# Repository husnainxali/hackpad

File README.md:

# Brokiepad – A 3x3 Macropad

### A simple and minimal 3*3 macropad with a built in oled display that can be customized to any use rn i have mapped it out as a gaming macropad using some of the basic keys that r needed while playing any game .

---
## Renders
- **PCB**

- **Case**

- **Explode view**

- **PCB layout**

- **Schematic**
 
<p align="center">
  <br>
 </p>

  ---
## BOM

Full parts list with quantities and costs: **[BOM.csv](BOM.csv)**

---
### Features:

- **9 Mechanical Switches**
- **OLED Display** 
- **12 SK6812MINI-E LEDs**
- **QMK Firmware**
- **Custom KiCad PCB**
- **3D-Printed Case**

---

## Keymap rn 

| Row | Key 1 | Key 2 | Key 3 |
|-----|-------|-------|-------|
| **1** | G | W | R |
| **2** | A | S | D |
| **3** | Left Shift | Space | Left Ctrl |

---
## Getting Started
- **Download PCB files and edit them according to your own need**
- **Download QMK MSYS**
- **Install Python and run `python3 -m pip install qmk` and then run `qmk setup` in terminal**
- **Download **[Brokiepad.uf2](Production/brokiepad.uf2)****
- **connect your macropad with a pc using a cable** 
- **Hold the boot button on the RP2040 board.**
- **Keep holding it while you plug the USB cable into your PC, then release the button.**
- **A drive named RPI-RP2 appears in File Explorer.**
- **Drag and drop your .uf2 file onto that drive.**
- **The drive disappears by itself after a few seconds and the board reboots as your macropad.**
- 
This project is licensed under the [MIT License](LICENSE).

---

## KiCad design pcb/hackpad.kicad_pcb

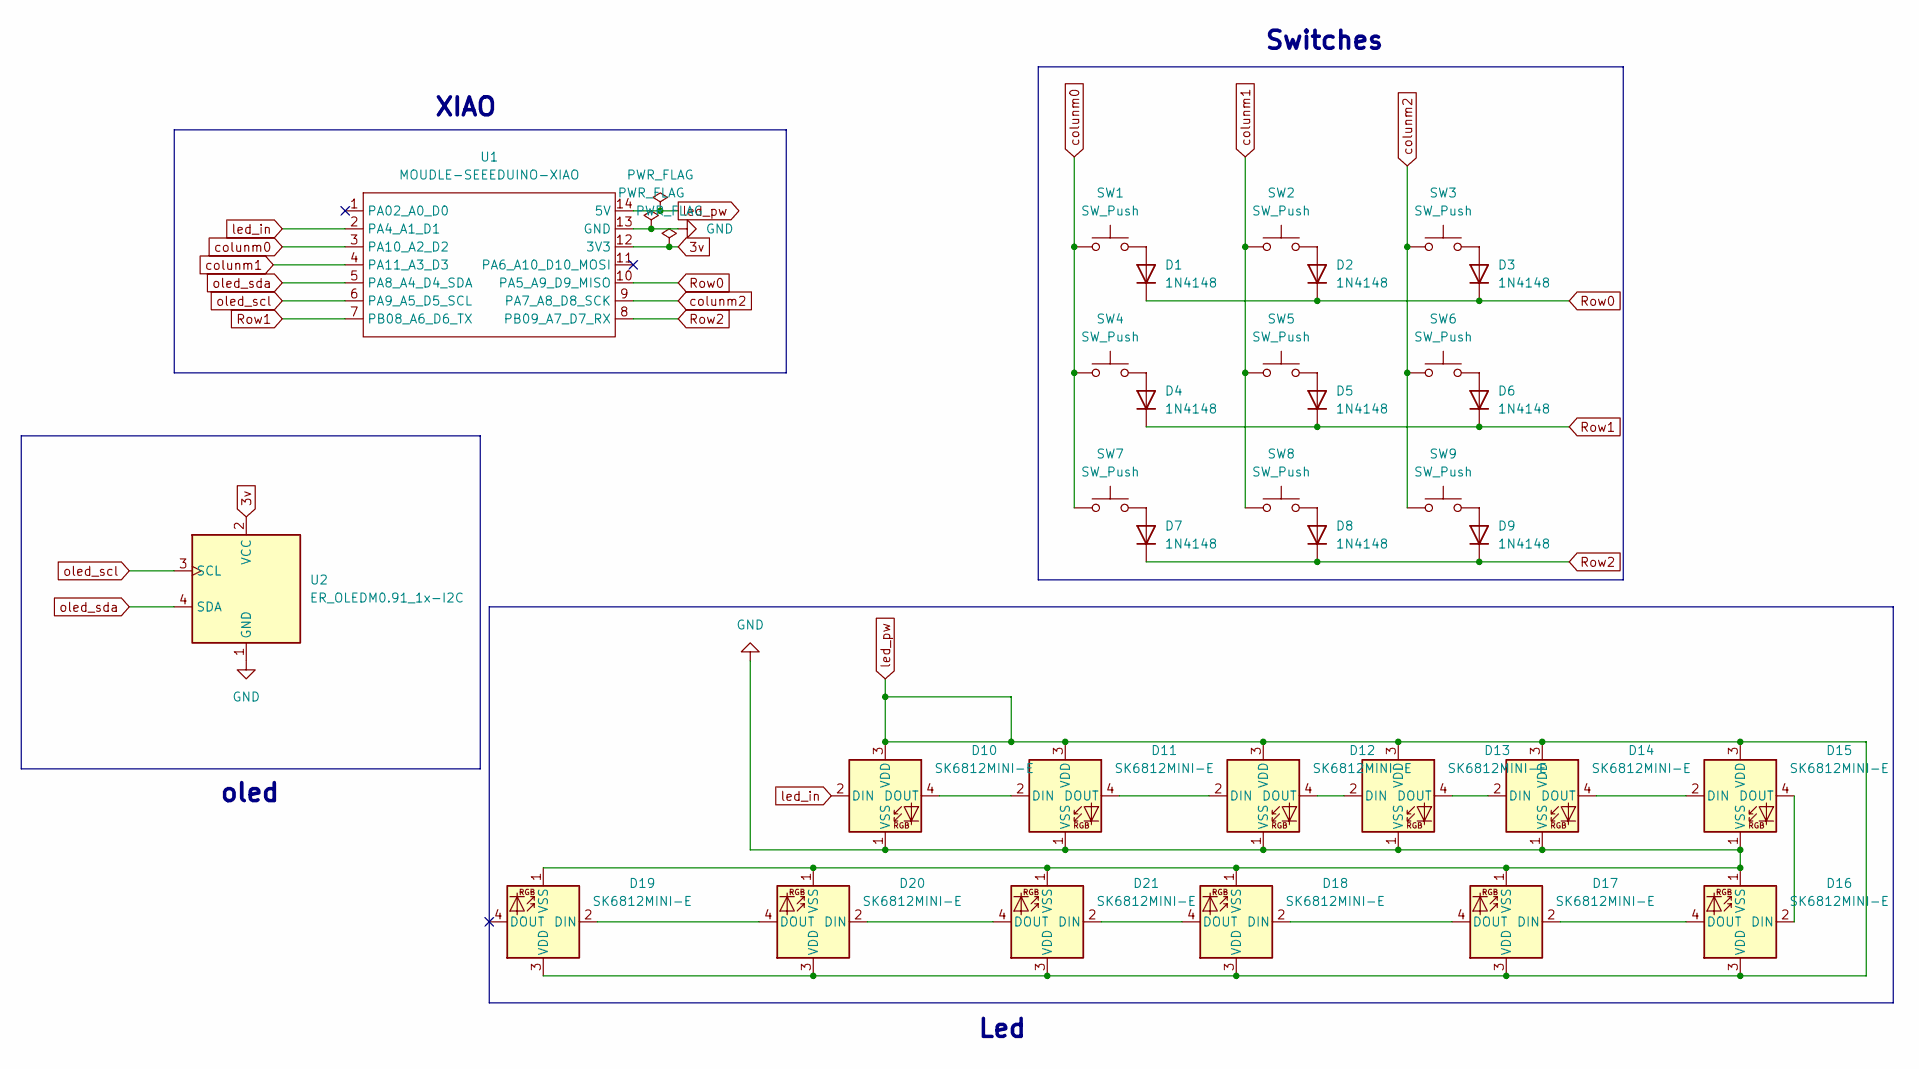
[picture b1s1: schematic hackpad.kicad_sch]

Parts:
D1, D2, D3, D4, D5, D6, D7, D8, D9: 1N4148; D_DO-35_SOD27_P7.62mm_Horizontal
D10, D11, D12, D13, D14, D15, D16, D17, D18, D19, D20, D21: SK6812MINI-E; LED_SK6812MINI-E_3.2x2.8mm_P1.5mm_ReverseMount
SW1, SW2, SW3, SW4, SW5, SW6, SW7, SW8, SW9: SW_Push; SW_Cherry_MX_1.00u_PCB
U1: MOUDLE-SEEEDUINO-XIAO; XIAO-Generic-Hybrid-14P-2.54-21X17.8MM
U2: ER_OLEDM0.91_1x-I2C

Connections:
3v: U1.12 (3V3), U2.2 (VCC)
GND: D10.1 (VSS), D11.1 (VSS), D12.1 (VSS), D13.1 (VSS), D14.1 (VSS), D15.1 (VSS), D16.1 (VSS), D17.1 (VSS), D18.1 (VSS), D19.1 (VSS), D20.1 (VSS), D21.1 (VSS), U1.13 (GND), U2.1 (GND)
unnamed: D1.2 (A), SW1.2
unnamed: D2.2 (A), SW2.2
unnamed: D3.2 (A), SW3.2
unnamed: D4.2 (A), SW4.2
unnamed: D5.2 (A), SW5.2
unnamed: D6.2 (A), SW6.2
unnamed: D7.2 (A), SW7.2
unnamed: D8.2 (A), SW8.2
unnamed: D9.2 (A), SW9.2
unnamed: D10.4 (DOUT), D11.2 (DIN)
unnamed: D11.4 (DOUT), D12.2 (DIN)
unnamed: D12.4 (DOUT), D13.2 (DIN)
unnamed: D13.4 (DOUT), D14.2 (DIN)
unnamed: D14.4 (DOUT), D15.2 (DIN)
unnamed: D15.4 (DOUT), D16.2 (DIN)
unnamed: D16.4 (DOUT), D17.2 (DIN)
unnamed: D17.4 (DOUT), D18.2 (DIN)
unnamed: D18.4 (DOUT), D21.2 (DIN)
unnamed: D19.2 (DIN), D20.4 (DOUT)
unnamed: D20.2 (DIN), D21.4 (DOUT)
Row0: D1.1 (K), D2.1 (K), D3.1 (K), U1.10 (PA5_A9_D9_MISO)
Row1: D4.1 (K), D5.1 (K), D6.1 (K), U1.7 (PB08_A6_D6_TX)
Row2: D7.1 (K), D8.1 (K), D9.1 (K), U1.8 (PB09_A7_D7_RX)
colunm0: SW1.1, SW4.1, SW7.1, U1.3 (PA10_A2_D2)
colunm1: SW2.1, SW5.1, SW8.1, U1.4 (PA11_A3_D3)
colunm2: SW3.1, SW6.1, SW9.1, U1.9 (PA7_A8_D8_SCK)
led_in: D10.2 (DIN), U1.2 (PA4_A1_D1)
led_pw: D10.3 (VDD), D11.3 (VDD), D12.3 (VDD), D13.3 (VDD), D14.3 (VDD), D15.3 (VDD), D16.3 (VDD), D17.3 (VDD), D18.3 (VDD), D19.3 (VDD), D20.3 (VDD), D21.3 (VDD), U1.14 (5V)
oled_scl: U1.6 (PA9_A5_D5_SCL), U2.3 (SCL)
oled_sda: U1.5 (PA8_A4_D4_SDA), U2.4 (SDA)

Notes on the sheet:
Led
Switches
XIAO
oled

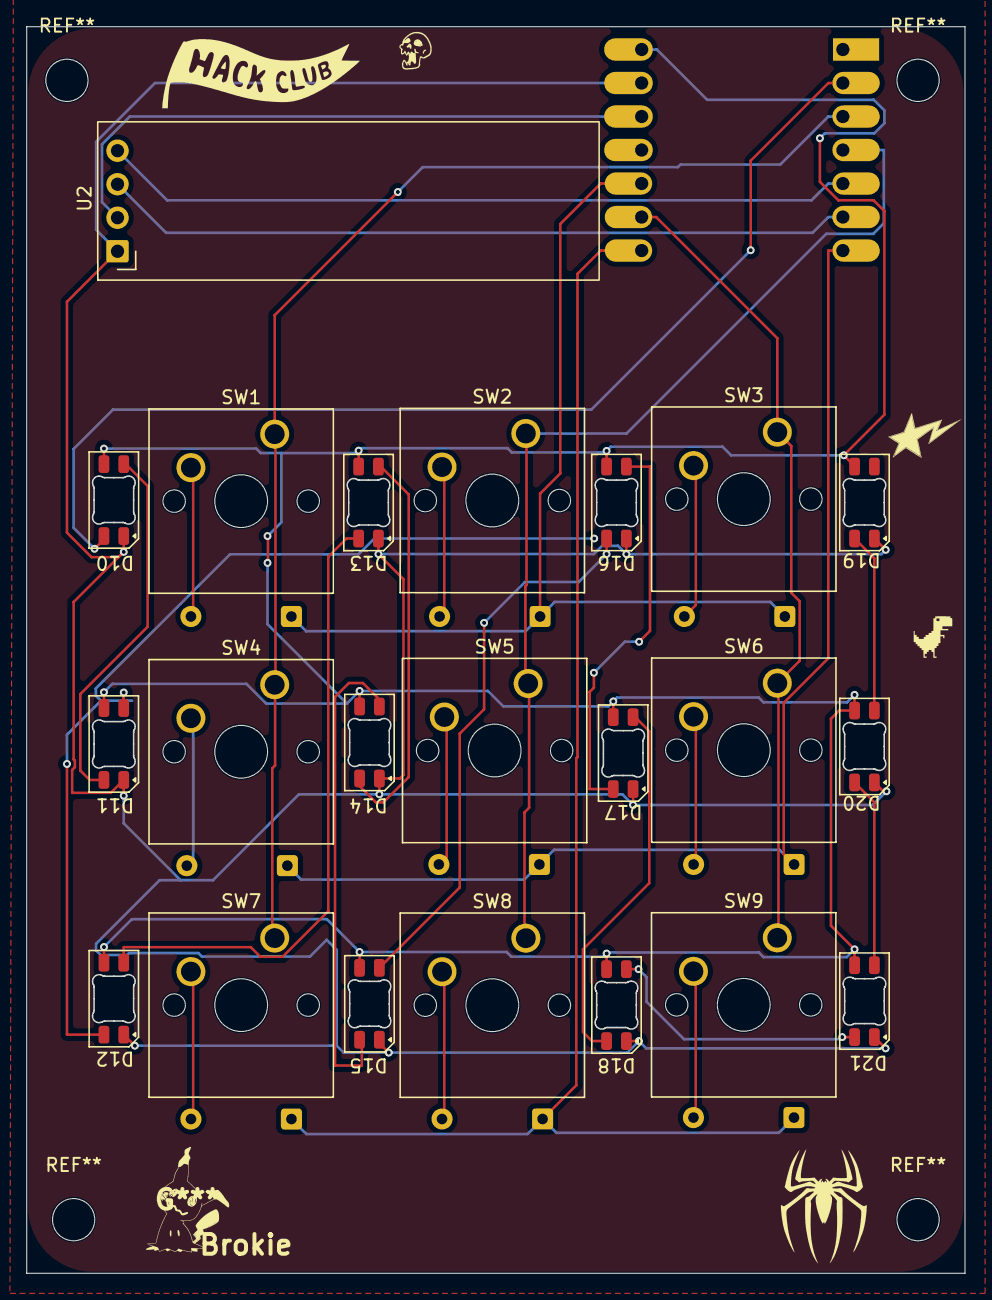
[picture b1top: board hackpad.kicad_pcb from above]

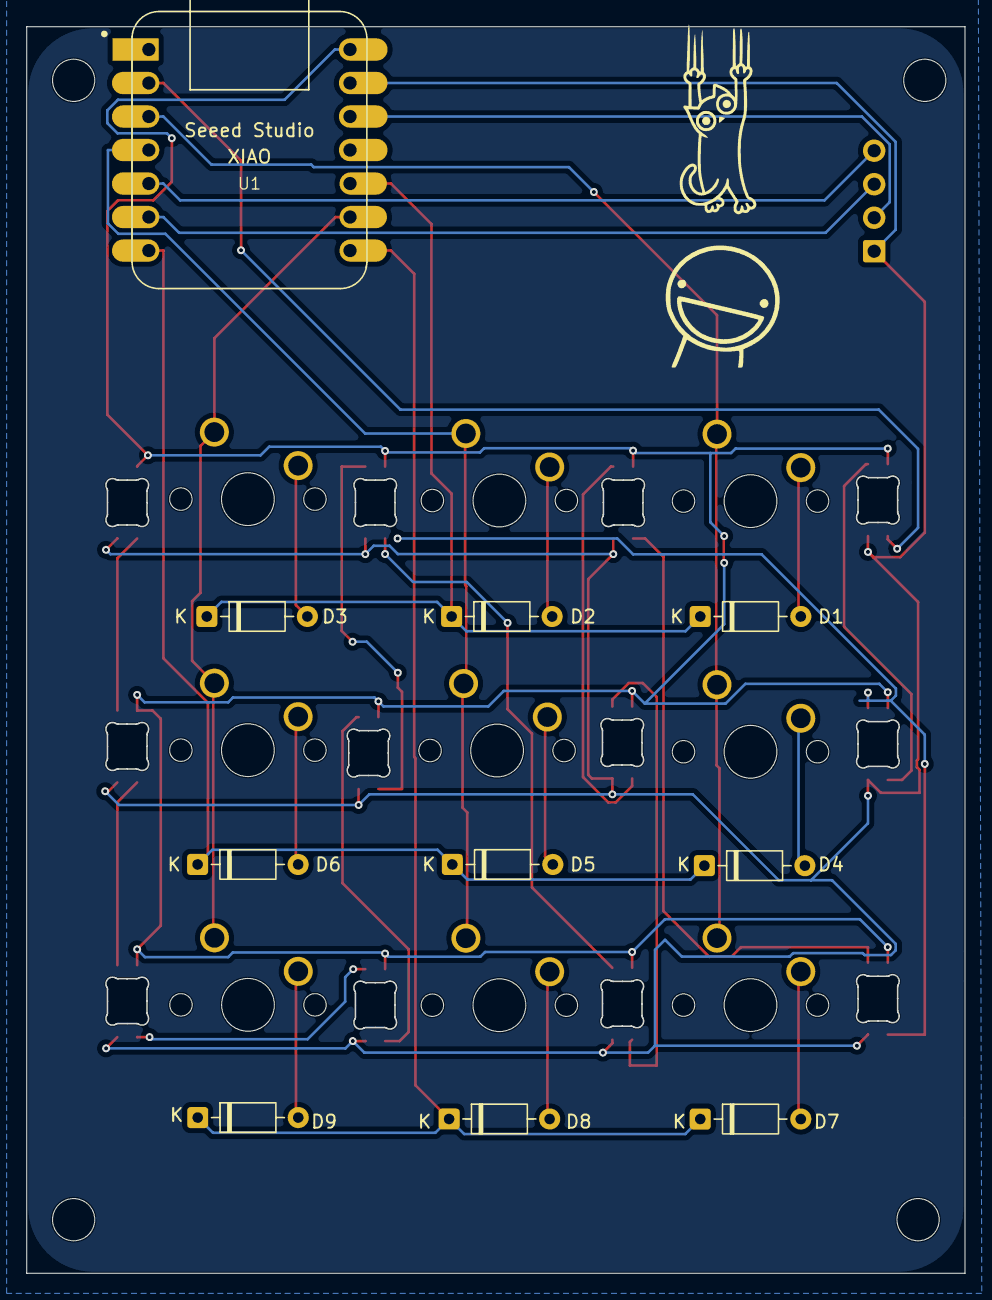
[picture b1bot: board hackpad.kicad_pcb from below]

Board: 2 copper layers, 71.1 x 94.5 mm, 32 parts (10 on the bottom side), 32 nets.
